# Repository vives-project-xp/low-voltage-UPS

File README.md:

# low-voltage-UPS

Project to make a low voltage UPS.
<!-- add better description -->

# Project Repository

This repository contains the source code and documentation for our project.

## Repository Structure

- `case`: Contains files related to the project's case design and 3D models.
- `esp-code`: Contains the code for the ESP micro controller used in the project.
- `frontend`: Contains the web frontend code for the project.
- `home-assistant`: Contains the configuration files for integrating the project with Home Assistant.
- `pcb`: Contains the PCB design files.
- `schemas`: Contains the schema diagrams for the project.

Link to video and ppt:
[Onedrive](https://vivesonline-my.sharepoint.com/:f:/g/personal/r0782899_student_vives_be/ErkIe6ZSpKdGq8MmYVde3NIBA33tiSL_xVnvaDJGF-avBQ?e=PaFOph)

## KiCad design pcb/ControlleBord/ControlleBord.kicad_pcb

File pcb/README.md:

# Circuit Board

## To do

1. vermogen verbruik van de aangesloten toestel.
2. gaten in de pcb maken.
3. kiezen tussen de batterij en net.
4. io pinnen maken 
5. soon^tm

## Schematic

## PCB

| Front | Back |
|---|---|
|  |  |

## BOM

The BOM or Bill of Materials consists out of a list of all the components with some of theire properties. 

| Designator | Quantity | Description | Footprint | Farnell ordercode | Price / unit |
|---|---|---|---|---|---|
| R25, R28-R30 | 4 | 1 kΩ | 0805 | [2073606](https://be.farnell.com/multicomp/mcmr08x1001ftl/res-1k-1-0-125w-0805-ceramic/dp/2073606) | 0,0165 € |
| R19 | 1 | 47.5 kΩ | 0805 | [2447665](https://be.farnell.com/multicomp/mcwr08x4752ftl/res-47k5-1-0-125w-thick-film/dp/2447665) | 0,0077 € |
| R18 | 1 | 22.1 kΩ | 0805 | [3496003](https://be.farnell.com/yageo/rc0805fr-0722k1l/res-22k1-1-0-125w-0805-thick-film/dp/3496003) | 0,029 € |
| R16, R17, R20, R22, R23 | 5 | 10 kΩ | 0805 | [1612522](https://be.farnell.com/bourns/cr0805-fx-1002elf/res-10k-1-0-125w-0805-thick-film/dp/1612522) | 0,029 € |
| R15 | 1 | 3.9 kΩ | 0805 | [2447654](https://be.farnell.com/multicomp/mcwr08x3901ftl/res-3k9-1-0-125w-thick-film/dp/2447654) | 0,0078 € |
| R14 | 1 | 1.5 kΩ | 0805 | [9333924](https://be.farnell.com/multicomp/mc01w080551k5/res-1k5-5-0-1w-0805-thick-film/dp/9333924) | 0,0153 € |
| R9 | 1 | 150 kΩ | 0805 | [2447573](https://be.farnell.com/multicomp/mcwr08x1503ftl/res-150k-1-0-125w-thick-film/dp/2447573) | 0,0078 € |
| R7, R8, R11-R13 | 5 | 10 Ω | 0805 | [2331768](https://be.farnell.com/te-connectivity/crgh0805j10r/res-10r-5-0-33w-0805-thick-film/dp/2331768) | 0,0132 € |
| R3-R5, R12, R13, R15 | 6 | 0.1 Ω | 0805 | [3994646](https://be.farnell.com/walsin/ww08xr100ftl/res-r100-0-125w-0805-thick-film/dp/3994646?st=shunt%20resistor) | 0,0302 € |
| R5 | 1 | 9.1 kΩ | 0805 | [2447739](https://be.farnell.com/multicomp/mcwr08x9101ftl/res-9k1-1-0-125w-thick-film/dp/2447739) | 0,0078 € |
| R4 | 1 | 82 kΩ | 0805 | [9237860](https://be.farnell.com/yageo/rc0805fr-0782kl/res-82k-1-0-125w-0805-thick-film/dp/9237860) | 0,029 € |
| R3 | 1 | 18 kΩ | 0805 | [2447584](https://be.farnell.com/multicomp/mcwr08x1802ftl/res-18k-1-0-125w-thick-film/dp/2447584) | 0,0078 € |
| R2 | 1 | 47 kΩ | 0805 | [9237836](https://be.farnell.com/yageo/rc0805fr-0747kl/res-47k-1-0-125w-0805-thick-film/dp/9237836) | 0,042 € |
| R1 | 1 | 51 kΩ | 0805 | [2447680](https://be.farnell.com/multicomp/mcwr08x5102ftl/res-51k-1-0-125w-0805-thick-film/dp/2447680) | 0,0081 € |
|---|---|---|---|---|---|
| C2 | 1 | 2.2 pF | 0805 | [3764575](https://be.farnell.com/yageo/cc0805crnpo9bn2r2/cap-2-2pf-50v-mlcc-0805/dp/3764575) | 0,0456 € |
| C5 | 1 | 47 pF | 0805 | [2812152](https://be.farnell.com/wurth-elektronik/885012007032/cap-47pf-25v-5-c0g-np0-0805/dp/2812152) | 0,047 € |
| C6, C7, C13, C17, C23 | 5 | 1μF | 0805 | [3873501](https://be.farnell.com/yageo/cc0805kkx6s8bb105/cap-1uf-25v-mlcc-0805/dp/3873501) | 0,0375 € |
| C8 | 1 | 10 nF | 0805 | [2534062](https://be.farnell.com/wurth-elektronik/885012207066/cap-0-01-f-25v-10-x7r-0805/dp/2534062) | 0,037 € |
| C3, C4, C10, C24 | 4 | 10 μF | 0805 | [3013452](https://be.farnell.com/samsung-electro-mechanics/cl21a106kaynnne/cap-10uf-25v-mlcc-0805/dp/3013452) | 0,073 € |
| C1, C11 | 1 | 470 μF | Radial Leaded | [9451439](https://be.farnell.com/multicomp/mcgpr50v477m13x21/cap-470-f-50v-20/dp/9451439) | 0,546 € |
| C12, C22 | 2 | 22 μF | 0805 | [1907510](https://be.farnell.com/murata/grm21br61e226me44l/cap-22-f-25v-20-x5r-0805/dp/1907510) | 0,178 € |
| C14 | 1 | 15 nF | 0805 | [2812419](https://be.farnell.com/wurth-elektronik/885012207067/cap-0-015-f-25v-10-x7r-0805/dp/2812419) | 0,0344 € |
| C9, C15, C19, C21, C23-C26, C29, C30 | 10 | 0.1 μF | 0805 | [2522443](https://be.farnell.com/kemet/c0805c104z3vactu/cap-0-1-f-25v-y5v-0805/dp/2522443) | 0,033 € |
| C16 | 1 | 2.2 μF | 0805 | [2073606](https://be.farnell.com/samsung-electro-mechanics/cl21a225kafnnne/cap-2-2uf-25v-mlcc-0805/dp/3013458) | 0,049 € |
| C18 | 1 | 33 μF | 1206 | [2525171](https://be.farnell.com/tdk/c3216x5r1e336m160ac/cap-33-f-25v-20-x5r-1206/dp/2525171) | 0,826 € |
| C20 | 1 | 100 pF | 0805 | [2812409](https://be.farnell.com/wurth-elektronik/885012207054/cap-100pf-25v-10-x7r-0805/dp/2812409) | 0,0468 € |
|---|---|---|---|---|---|
| J1, J2, J4 | 3 | 2 ways | screw terminal | [3810178](https://be.farnell.com/amphenol-anytek/yo0221500000g/tb-wire-to-brd-r-a-2way-16awg/dp/3810178) | 0,455 € |
|---|---|---|---|---|---|
| U7-U10, U13, U15 | 6 | Switch | Switch | [2320087](https://be.farnell.com/c-k-components/pts645sm43smtr92lfs/switch-spst-0-05a-12vdc-smd-4/dp/2320087) | 0,25 € |
|---|---|---|---|---|---|
| J5 | 1 | USB connector | USB | [2554980](https://be.farnell.com/hirose-hrs/zx62d-b-5p8-30/micro-usb-2-0-type-b-rcpt-smt/dp/2554980?st=zx62d-b-5p8) | 0,846 € |
| U14 | 1 | ESD Protection Device | SOT-23 | [2290332](https://be.farnell.com/kingbright/kp-2012seck/led-0805-250mcd-orange/dp/2290332) | 0,159 € |
|---|---|---|---|---|---|
| SR1 | 1 | diode | DO-214 | [2101195](https://be.farnell.com/multicomp/ss34a/diode-rectifier-3a-40v-do-214ac/dp/2101195?st=ss34) | 0,401 € |
| D1 - D3 | 3 | led | 0805 | [2101195](https://be.farnell.com/multicomp/ss34a/diode-rectifier-3a-40v-do-214ac/dp/2101195?st=ss34) | 0,401 € |
|---|---|---|---|---|---|
| U6 | 1 | I2c potentiometer | MSOP | [8737606](https://be.farnell.com/microchip/mcp4531-103e-ms/dpot-single-7bit-v-i2c-8msop/dp/1698946?st=digital%20potentiometer) |0,40 € |
|---|---|---|---|---|---|
| L1 | 1 | 6.8 μH | YUP | [3518424](https://nl.farnell.com/wurth-elektronik/7447720068/inductor-6-8uh-unshielded-3-9a/dp/3518424) | € 0,756 |
| L2 | 1 | 33 μH | YUP | [2061655](https://nl.farnell.com/bourns/srn6045-330m/inductor-33uh-semi-shielded-power/dp/2061655) | € 0,408 |
| L3 | 1 | 49 μH | YUP | [3517136](https://nl.farnell.com/wurth-elektronik/744132/toroidal-inductor-49uh-5-8a-tht/dp/3517136) | € 2,56 |
|---|---|---|---|---|---|
| U3, U5 | 1 | 10 kΩ | SOIC | [3517136](https://be.farnell.com/texas-instruments/ina219bidr/current-power-monitor-11khz-soic/dp/3118166?st=ina219) | 2,96 € |
|---|---|---|---|---|---|
| U1 | 1 | Buck | SOIC | [3755444](https://be.farnell.com/diodes-inc/pam2421aecadjr/dc-dc-conv-boost-520khz-40-to/dp/3755444?st=pam2421) | 0,90 € |
| U2 | 1 | Buck| SOIC | [4064213](https://be.farnell.com/stmicroelectronics/l6981c33dr/dc-dc-conv-sync-buck-400khz-150deg/dp/4064213?st=l6981c) | 3,02 € |
| U4 | 1 | Buck | QFN-34 | [2355372](https://be.farnell.com/onsemi/fan23sv10mmpx/buck-synch-adj-10a-1-5mhz-34pqfn/dp/2355372?st=fan23sv10m) | 1,72 € |
|---|---|---|---|---|---|
| Q2 | 1 | P-kanaal | TO-220 | [8648620](https://be.farnell.com/infineon/irf9540npbf/mosfet-p-100v-23a-to-220/dp/8648620) | 1,55 € |
| Q1 | 1 | N-kanaal | TO-220 | [2547307](https://be.farnell.com/vishay/irfz34pbf/mosfet-n-ch-60v-30a-to-220ab-3/dp/2547307) | 1,96 € |

Total price: 65,03 €

| Designator | Quantity | Description | Footprint | Mouser ordercode | Price / unit |
|---|---|---|---|---|---|
| U12 | 1 | ESP32-S3 | ESP32 | [C2913202](https://www.lcsc.com/product-detail/WiFi-Modules_Espressif-Systems-ESP32-S3-WROOM-1-N16R8_C2913202.html) | € 4.83 |
| U11 | 1 | CP2102NA02GQFN28 | QFN28 | [C964632](https://www.lcsc.com/product-detail/USB-ICs_SILICON-LABS-CP2102N-A02-GQFN28R_C964632.html) | € 2.60 |

Total price: €10.26

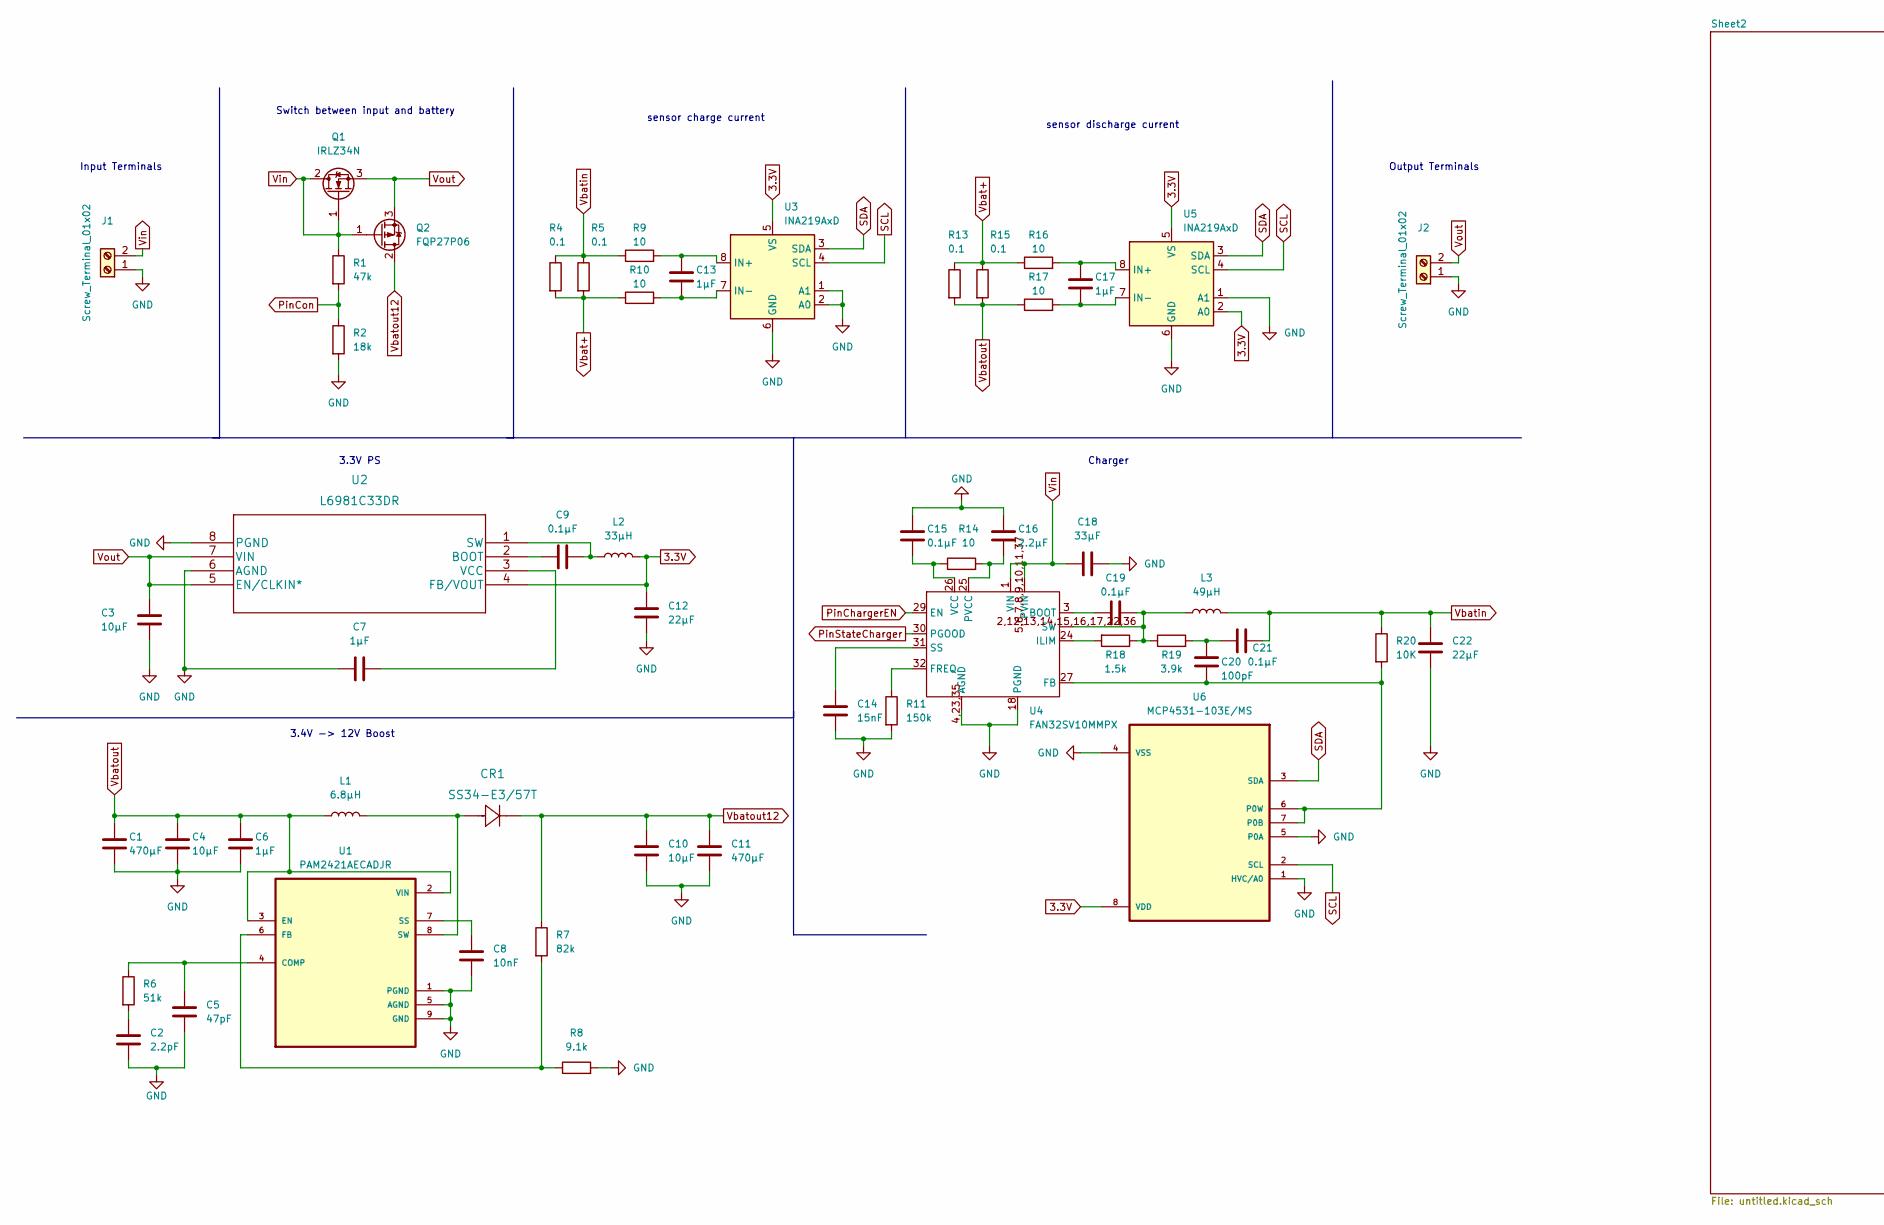
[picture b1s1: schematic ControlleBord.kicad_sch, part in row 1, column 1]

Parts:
C1, C11: 470μF; CP_Radial_D13.0mm_P5.00mm
C2: 2.2pF; C_0805_2012Metric
C3, C4, C10: 10μF; C_0805_2012Metric
C5: 47pF; C_0805_2012Metric
C6, C7, C13, C17: 1μF; C_0805_2012Metric
C8: 10nF; C_0805_2012Metric
C9, C15, C19, C21: 0.1μF; C_0805_2012Metric
C12, C22: 22μF; C_0805_2012Metric
C14: 15nF; C_0805_2012Metric
C16: 2.2μF; C_0805_2012Metric
C18: 33μF; C_1206_3216Metric
C20: 100pF; C_0805_2012Metric
CR1: SS34-E3/57T; SS34-E3&slash_57T
J1, J2: Screw_Terminal_01x02; YO0221500000G
L1: 6.8μH; L_Toroid_Vertical_L26.7mm_W14.0mm_P10.16mm_Pulse_D
L2: 33μH; L_Bourns_SRN6045TA
L3: 49μH; L_Toroid_Vertical_L21.6mm_W9.1mm_P8.40mm_Bourns_5700
Q1: IRLZ34N; TO-220-3_Vertical
Q2: FQP27P06; TO-220-3_Vertical
R1: 47k; R_0805_2012Metric
R2: 18k; R_0805_2012Metric
R4, R5, R13, R15: 0.1; R_2512_6332Metric
R6: 51k; R_0805_2012Metric
R7: 82k; R_0805_2012Metric
R8: 9.1k; R_0805_2012Metric
R9, R10, R14, R16, R17: 10; R_0805_2012Metric
R11: 150k; R_0805_2012Metric
R18: 1.5k; R_0805_2012Metric
R19: 3.9k; R_0805_2012Metric
R20: 10K; R_0805_2012Metric
U1: PAM2421AECADJR; SOIC127P600X175-8N
U2: L6981C33DR
U3, U5: INA219AxD; SOIC-8_3.9x4.9mm_P1.27mm
U4: FAN32SV10MMPX; FAN23SV10M
U6: MCP4531-103E/MS; SOP65P490X110-8N

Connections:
3.3V: C12.1, L2.2, U2.4 (FB/VOUT), U3.5 (VS), U5.2 (A0), U5.5 (VS), U6.8 (VDD); also elsewhere on the board
GND: C1.2, C2.2, C3.2, C4.2, C5.2, C6.2, C7.1, C8.2, C10.2, C11.2, C12.2, C14.2, C15.1, C16.1, C18.2, C22.2, J1.1, J2.1, R2.2, R8.2, R11.2, U1.1 (PGND), U1.5 (AGND), U1.9 (GND), U2.6 (AGND), U2.8 (PGND), U3.1 (A1), U3.2 (A0), U3.6 (GND), U4.4,23,35 (AGND), U4.18 (PGND), U5.1 (A1), U5.6 (GND), U6.1 (HVC/A0), U6.4 (VSS), U6.5 (P0A); also elsewhere on the board
unnamed: C2.1, R6.2
unnamed: C5.1, R6.1, U1.4 (COMP)
unnamed: C7.2, U2.3 (VCC)
unnamed: C8.1, U1.7 (SS)
unnamed: C9.1, U2.2 (BOOT)
unnamed: C9.2, L2.1, U2.1 (SW)
unnamed: C13.1, R9.2, U3.8 (IN+)
unnamed: C13.2, R10.2, U3.7 (IN-)
unnamed: C14.1, U4.31 (SS)
unnamed: C15.2, R14.1, U4.26 (VCC)
unnamed: C16.2, R14.2, U4.25 (PVCC)
unnamed: C17.1, R16.2, U5.8 (IN+)
unnamed: C17.2, R17.2, U5.7 (IN-)
unnamed: C19.1, U4.3 (BOOT)
unnamed: C19.2, L3.1, R18.1, R19.1, U4.2,12,13,14,15,16,17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 (SW)
unnamed: C20.1, C21.1, R19.2
unnamed: C20.2, R20.2, U4.27 (FB), U6.6 (P0W), U6.7 (P0B)
unnamed: CR1.2, L1.2, U1.8 (SW)
unnamed: R7.2, R8.1, U1.6 (FB)
unnamed: R11.1, U4.32 (FREQ)
unnamed: R18.2, U4.24 (ILIM)
PinChargerEN: U4.29 (EN); also elsewhere on the board
PinCon: R1.2, R2.1; also elsewhere on the board
PinStateCharger: U4.30 (PGOOD); also elsewhere on the board
SCL: U3.4 (SCL), U5.4 (SCL), U6.2 (SCL); also elsewhere on the board
SDA: U3.3 (SDA), U5.3 (SDA), U6.3 (SDA); also elsewhere on the board
Vbat+: R4.2, R5.2, R10.1, R13.1, R15.1, R16.1; also elsewhere on the board
Vbatin: C21.2, C22.1, L3.2, R4.1, R5.1, R9.1, R20.1
Vbatout: C1.1, C4.1, C6.1, L1.1, R13.2, R15.2, R17.1, U1.2 (VIN), U1.3 (EN); also elsewhere on the board
Vbatout12: C10.1, C11.1, CR1.1, Q2.2 (D), R7.1; also elsewhere on the board
Vin: C18.1, J1.2, Q1.1 (G), Q1.2 (D), Q2.1 (G), R1.1, U4.1 (VIN), U4.5,6,7,8,9,10,11,37 (PVIN)
Vout: C3.1, J2.2, Q1.3 (S), Q2.3 (S), U2.5 (EN/CLKIN*), U2.7 (VIN)

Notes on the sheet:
Charger
Input Terminals
Switch between input and battery
sensor charge current
sensor discharge current
Output Terminals
3.3V PS
3.4V -> 12V Boost

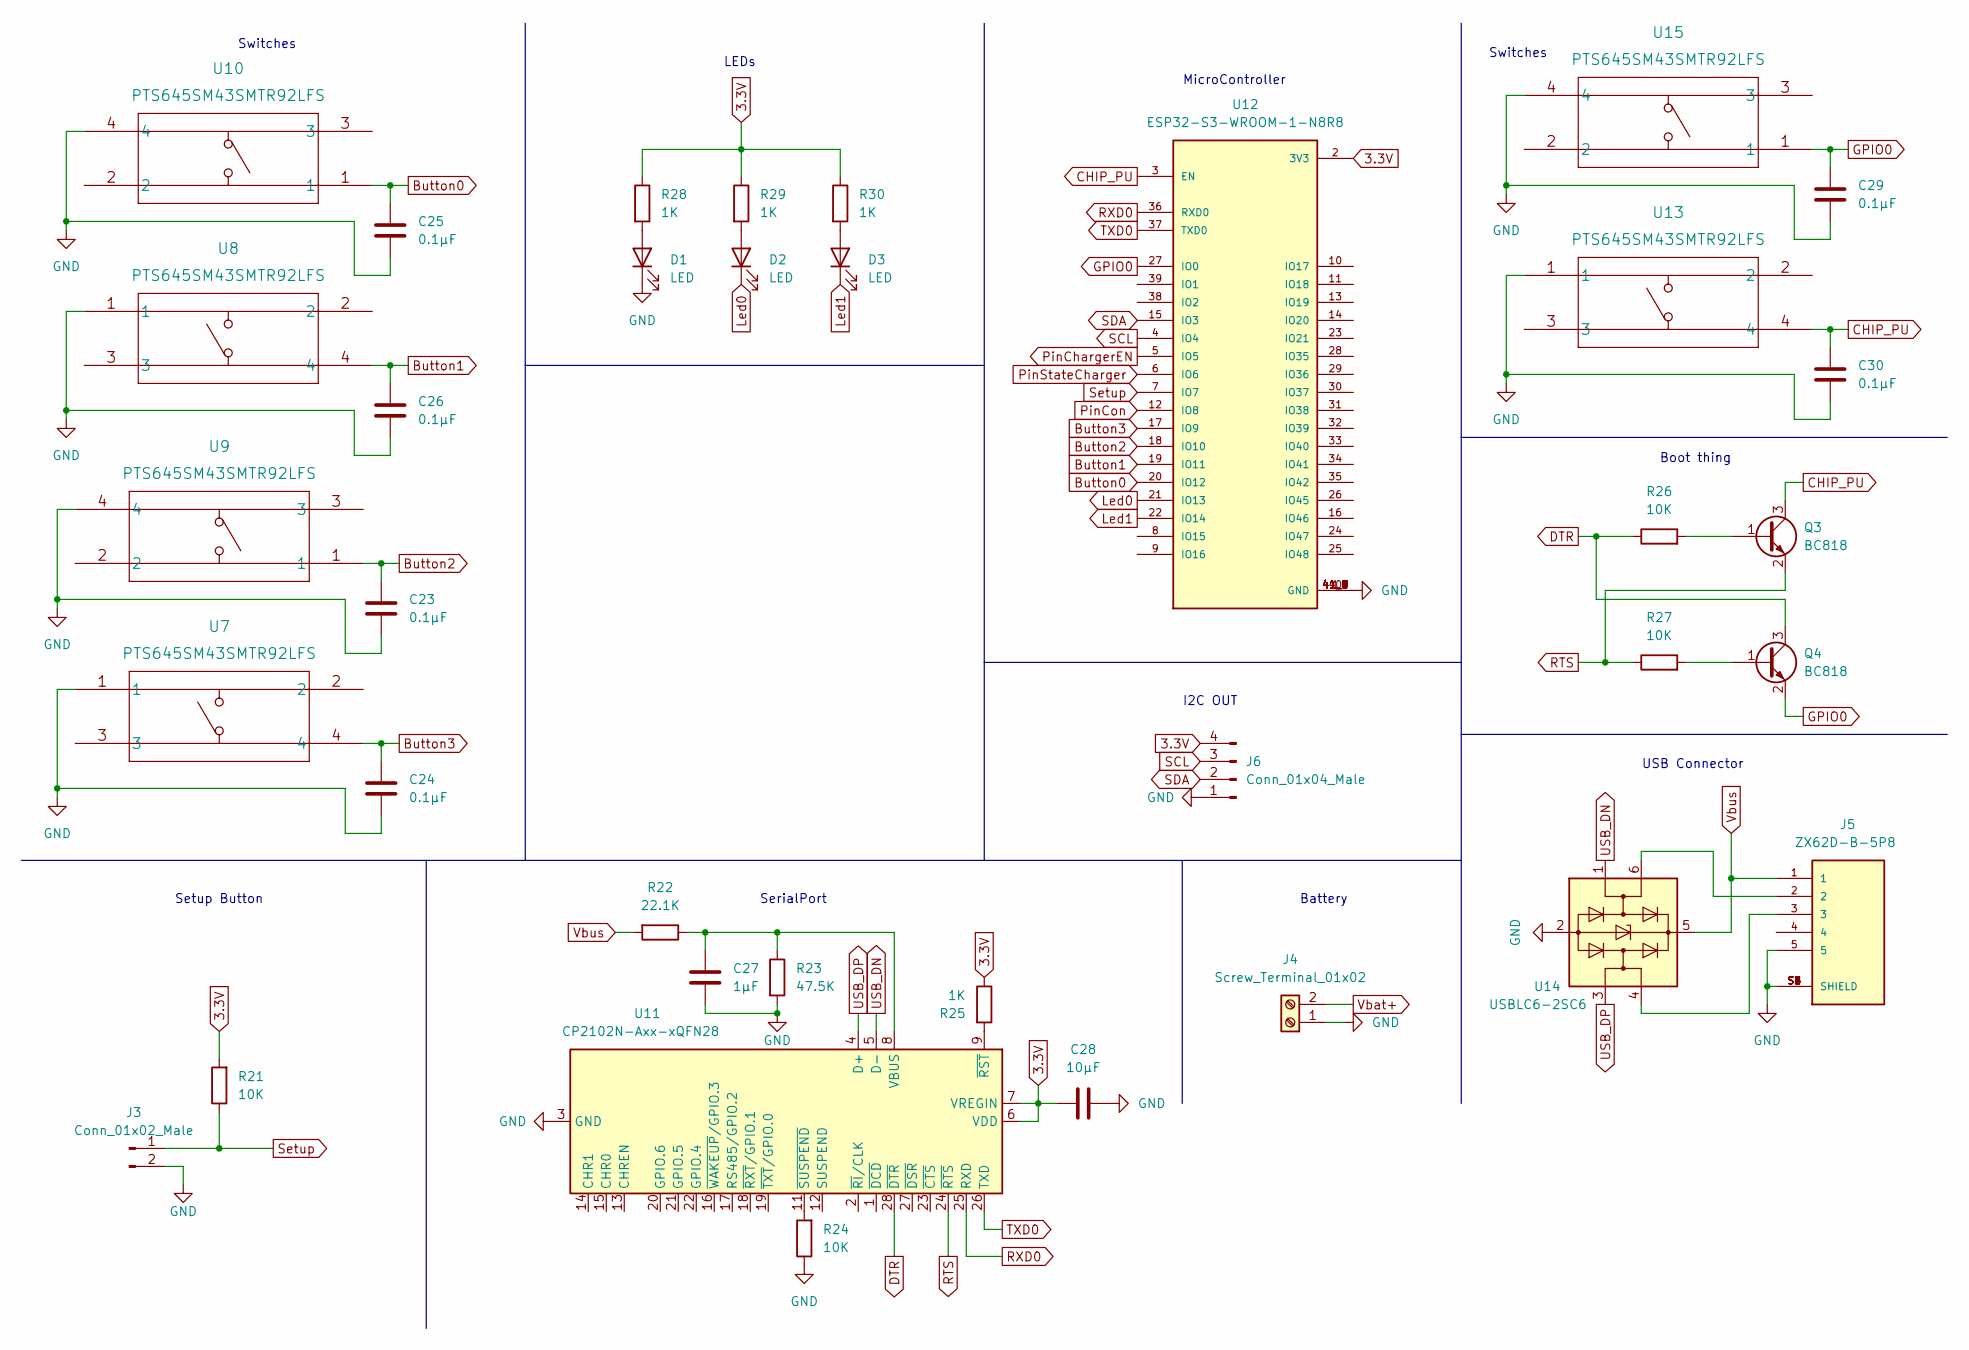
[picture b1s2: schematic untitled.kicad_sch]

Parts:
C23, C24, C25, C26, C29, C30: 0.1μF; C_0805_2012Metric
C27: 1μF; C_0805_2012Metric
C28: 10μF; C_0805_2012Metric
D1, D2, D3: LED; R_0805_2012Metric
J3: Conn_01x02_Male; PinHeader_1x02_P2.54mm_Vertical
J4: Screw_Terminal_01x02; YO0221500000G
J5: ZX62D-B-5P8; HRS_ZX62D-B-5P8; PARTREV N/A
J6: Conn_01x04_Male; PinSocket_1x04_P2.54mm_Vertical
Q3, Q4: BC818; SOT-23
R21, R24, R26, R27: 10K; R_0805_2012Metric
R22: 22.1K; R_0805_2012Metric
R23: 47.5K; R_0805_2012Metric
R25, R28, R29, R30: 1K; R_0805_2012Metric
U7, U8, U9, U10, U13, U15: PTS645SM43SMTR92LFS
U11: CP2102N-Axx-xQFN28; QFN-28-1EP_5x5mm_P0.5mm_EP3.35x3.35mm
U12: ESP32-S3-WROOM-1-N8R8; XCVR_ESP32S3WROOM1N8R8
U14: USBLC6-2SC6; SOT-23-6

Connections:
3.3V: C28.1, J6.4, R21.2, R25.1, R28.1, R29.1, R30.1, U11.6 (VDD), U11.7 (VREGIN), U12.2 (3V3); also elsewhere on the board
Button0: C25.2, U10.1, U12.20 (IO12)
Button1: C26.1, U8.4, U12.19 (IO11)
Button2: C23.2, U9.1, U12.18 (IO10)
Button3: C24.1, U7.4, U12.17 (IO9)
CHIP_PU: C30.1, Q3.3 (C), U12.3 (EN), U13.4
DTR: Q4.3 (C), R26.1, U11.28 (~DTR)
GND: C23.1, C24.2, C25.1, C26.2, C27.2, C28.2, C29.1, C30.2, D1.1 (K), J3.2, J4.1, J5.5, J5.S1 (SHIELD), J5.S2 (SHIELD), J5.S3 (SHIELD), J5.S4 (SHIELD), J5.S5 (SHIELD), J5.S6 (SHIELD), J6.1, R23.2, R24.1, U7.1, U8.1, U9.4, U10.4, U11.3 (GND), U11.29 (GND), U12.1 (GND), U12.40 (GND), U12.41_1 (GND), U12.41_2 (GND), U12.41_3 (GND), U12.41_4 (GND), U12.41_5 (GND), U12.41_6 (GND), U12.41_7 (GND), U12.41_8 (GND), U12.41_9 (GND), U13.1, U14.2 (GND), U15.4; also elsewhere on the board
GPIO0: C29.2, Q4.2 (E), U12.27 (IO0), U15.1
Led0: D2.1 (K), U12.21 (IO13)
Led1: D3.1 (K), U12.22 (IO14)
unnamed: C27.1, R22.1, R23.1, U11.8 (VBUS)
unnamed: D1.2 (A), R28.2
unnamed: D2.2 (A), R29.2
unnamed: D3.2 (A), R30.2
unnamed: J5.2, U14.6 (I/O1)
unnamed: J5.3, U14.4 (I/O2)
unnamed: Q3.1 (B), R26.2
unnamed: Q4.1 (B), R27.2
unnamed: R24.2, U11.11 (~SUSPEND)
unnamed: R25.2, U11.9 (~RST)
PinChargerEN: U12.5 (IO5); also elsewhere on the board
PinCon: U12.12 (IO8); also elsewhere on the board
PinStateCharger: U12.6 (IO6); also elsewhere on the board
RTS: Q3.2 (E), R27.1, U11.24 (~RTS)
RXD0: U11.25 (RXD), U12.36 (RXD0)
SCL: J6.3, U12.4 (IO4); also elsewhere on the board
SDA: J6.2, U12.15 (IO3); also elsewhere on the board
Setup: J3.1, R21.1, U12.7 (IO7)
TXD0: U11.26 (TXD), U12.37 (TXD0)
USB_DN: U11.5 (D-), U14.1 (I/O1)
USB_DP: U11.4 (D+), U14.3 (I/O2)
Vbat+: J4.2; also elsewhere on the board
Vbus: J5.1, R22.2, U14.5 (VBUS)

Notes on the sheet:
SerialPort
USB Connector
Setup Button
Switches
MicroController
LEDs
Battery
I2C OUT
Boot thing

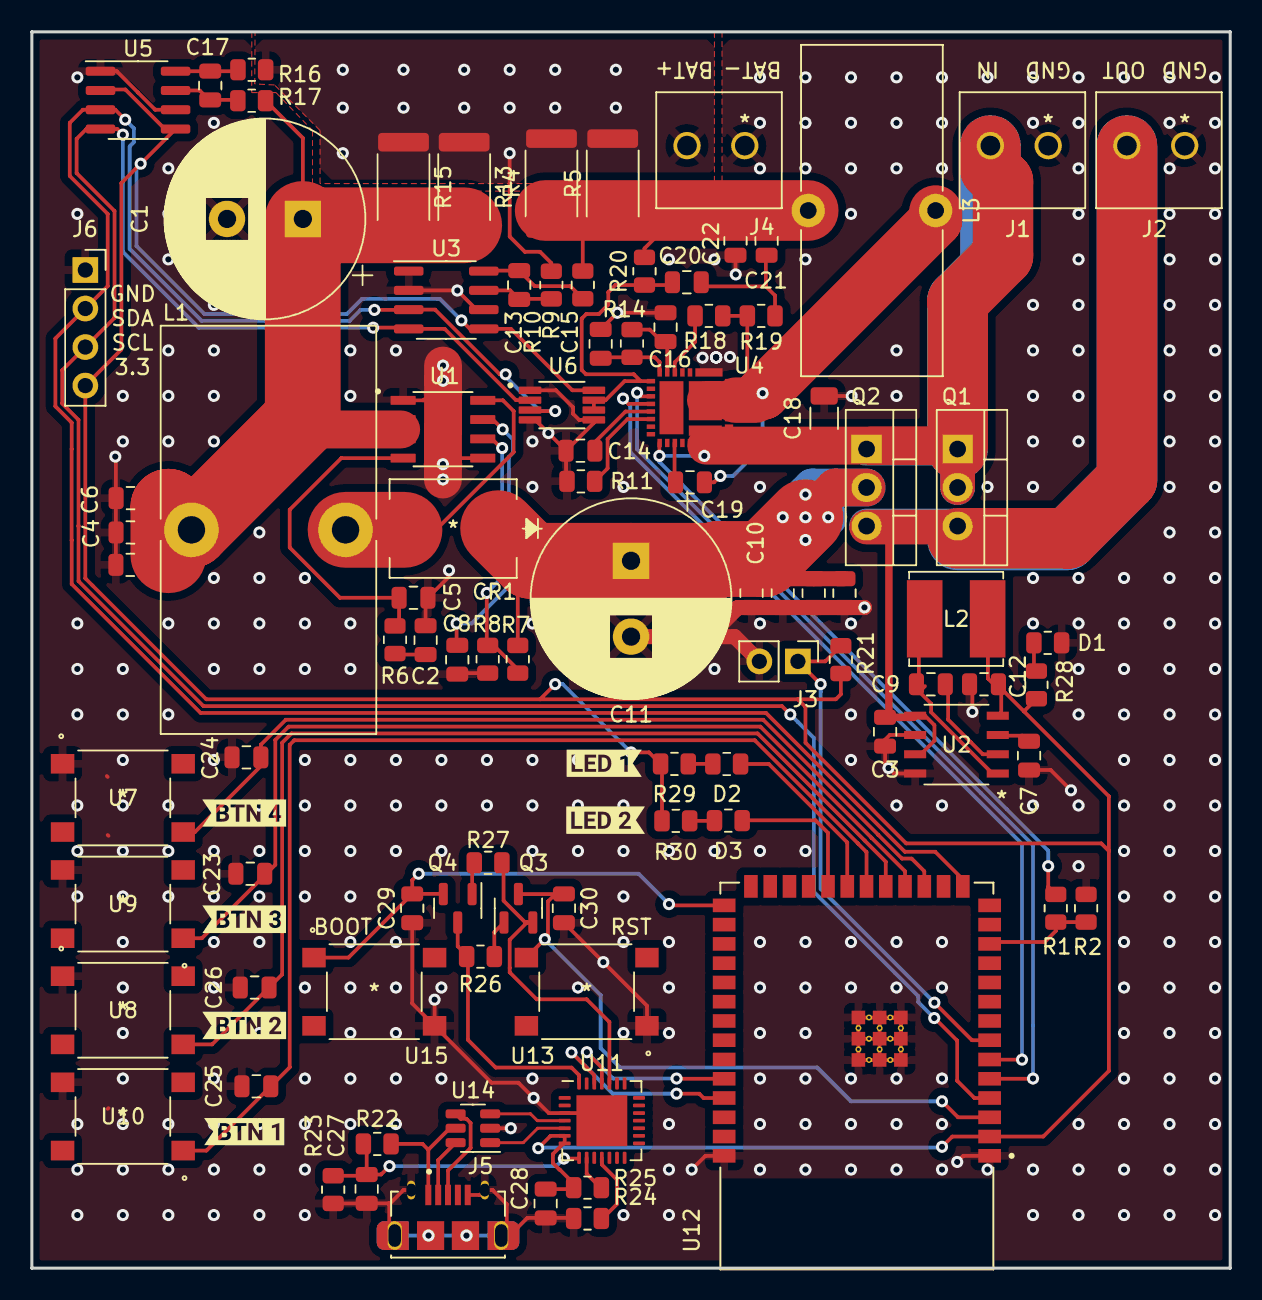
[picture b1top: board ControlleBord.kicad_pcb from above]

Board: 2 copper layers, 79.0 x 81.5 mm, 100 parts (0 on the bottom side), 60 nets.

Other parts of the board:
C4#2, C10#2, C10#3, C10#4: 10μF; C_0805_2012Metric
kibuzzard-6409D4B5: G***; kibuzzard-6409D4B5
kibuzzard-6409D4BC: G***; kibuzzard-6409D4BC
kibuzzard-6409D4C2: G***; kibuzzard-6409D4C2
kibuzzard-6409D4D1: G***; kibuzzard-6409D4D1
kibuzzard-6409D47A: G***; kibuzzard-6409D47A
kibuzzard-6409D460: G***; kibuzzard-6409D460

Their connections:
GND: C4#2.2, C10#2.2, C10#3.2, C10#4.2; also elsewhere on the board
Vbatout: C4#2.1; also elsewhere on the board
Vbatout12: C10#2.1, C10#3.1, C10#4.1; also elsewhere on the board

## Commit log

2023-03-02 initial compose
2023-03-02 working docker-compose not configured yet
2023-03-02 docker compose v2
2023-03-02 Made Bom and schematics.
2023-03-02 docker compose v3
2023-03-02 Moved pcb files to folder
2023-03-03 Initial commit of frontend using nuxt (vue)
2023-03-03 added link back to homepage
2023-03-03 added very basic footer
2023-03-03 published build and added to link to readme
2023-03-03 added contact page
2023-03-03 edit content of template pages
2023-03-04 removed unnecessary div
2023-03-04 added tailwind css to project
2023-03-04 did some styling for the default layout
2023-03-05 added padding to content
2023-03-05 added drak mode (system default)
2023-03-05 fixed page mistake
2023-03-05 update Home Assistent
2023-03-05 changed theme color
2023-03-05 made homepage modular
2023-03-05 eddited layout theme
2023-03-05 added axample content to setup page
2023-03-06 adding dark-mode button
2023-03-07 just dark theme
2023-03-07 removed unnecessary file
2023-03-07 switched setup and about page on header
2023-03-08 add other plugins @nuxtjs/tailwindcss , color-mode
2023-03-08 custom style works with tailwind
2023-03-08 dropdown dark mode button
2023-03-08 custom style adds darkmode theme
2023-03-09 switched to purple theme
2023-03-09 added daisyui (tailwind plugin)
2023-03-09 removed all theming
2023-03-09 ESP code added, wifi and mqtt basic example working
2023-03-09 Switched to only one layout (inside app.vue)
2023-03-09 switched drawer to end (right side)
2023-03-09 homeassistant new working config
2023-03-09 mossquito conf update
2023-03-09 update docker compose file
2023-03-09 add groups.yaml
2023-03-09 add pcb files
2023-03-09 added imges to README.md
2023-03-09 changed header title
2023-03-09 overide custom themes
2023-03-09 added title block to home page
2023-03-09 Added fixed height to homepage title bock
2023-03-09 global update to create parallel with main branch
2023-03-13 Added more content for testing purposes
2023-03-13 fixed section spacing
2023-03-13 Created seperate Header and Footer modules
2023-03-13 Fixed header color
2023-03-13 removed hero to fix header bug, bg opacity is gone
2023-03-13 Moved back to layout file
2023-03-14 local storage mqtt data
2023-03-14 adding gitignore
2023-03-14 adding comments mosquitto.conf
2023-03-14 adding more to ha configuration
2023-03-14 update gitignore
2023-03-15 added some links to readme
2023-03-15 Added testing content to setup page
2023-03-15 added vueuse for bluetooth functionality
2023-03-15 First implementation of bluetooth
2023-03-15 added dark filter over bg image
2023-03-16 adding comments
2023-03-16 added bluetooth services and chars for testing
2023-03-16 fixing typo's
2023-03-16 fixing more typo's
2023-03-16 adding sensor
2023-03-16 Added schema's
2023-03-16 made bluetooth work (without module)
2023-03-16 fixing typo
2023-03-16 moved to export default
2023-03-16 made changess to readme
2023-03-16 misc
2023-03-16 added multiple characteristic
2023-03-18 first try at blueprint
2023-03-18 adding first try blueprint
2023-03-18 refining mqtt devices
2023-03-18 changing order
2023-03-18 trying to create automation blueprint
2023-03-18 first draft of the readme
2023-03-23 adding full config of HA localy
2023-03-23 adding local config
2023-03-23 updating gitignore
2023-03-23 show all bluetooth devices
2023-03-23 Added pagetitle component
2023-03-23 updated setup page
2023-03-23 updated ssid characteristic
2023-03-23 blueprints with deprecated group.set
2023-03-23 updating HA
2023-03-23 adding group.yaml
2023-03-23 adding dwain
2023-03-23 fixing battery charge
2023-03-23 dwains dashboard
2023-03-23 updated setup to use Composition API
2023-03-23 added page title for contact page
2023-03-23 added content to about page
2023-03-30 dwains dashboard config
2023-03-30 mqtt.yaml
2023-03-30 typo fix
2023-03-30 adding hacs
2023-03-30 adding dependencies
2023-03-30 gitignore update
2023-04-12 added first version of cdem device
2023-04-13 v2 of cdem ha integration
2023-04-13 v3 of cdem ha integration
2023-04-13 v4 of cdem ha integration
2023-04-18 Added IO map and I2C adresses to Schemas
2023-04-20 typo fix 'web site' to 'website'
2023-04-20 updating deprecated dependencties
2023-04-20 adding more function to the connect button
2023-04-20 mqtt broker input field adding default port 1883
2023-04-20 reformatted setup page
2023-04-20 added comments
2023-04-20 reformat setup page code
2023-04-20 added empty files for homeasssistant schemas
2023-04-20 adding custom css root colors
2023-04-20 adding packages color-mode, nuxtjs/tailwindcss
2023-04-20 update default text color
2023-04-20 changed file type for better loading times
2023-04-20 adding custom css class
2023-04-20 applying new css style to all pages
2023-04-20 added other drawio backup format to gitignore
2023-04-20 added some flowcharts
2023-04-20 added python cache to gitignore
2023-04-20 adding style
2023-04-20 small reformating setting page
2023-04-26 removed link to contact page
2023-04-26 changed style
2023-04-26 changed the default vue page width
2023-04-26 changed style and content of the about page
2023-04-26 changed style and content setup page
2023-04-26 added content to index page
2023-04-27 updated the todo list
2023-04-27 updated the todo list 2.0
2023-04-27 fixed mqtt port
2023-04-27 fixed ip port bug setup page
2023-04-27 added some documentation to program MCP4531
2023-04-27 added dns resolving and ip validation
2023-04-27 adjusted style and adding responsive cards
2023-04-27 made more responsive
2023-04-27 adding password viewer setup page
2023-04-27 removed redundend packages
2023-04-27 adding responsiveness
2023-04-27 adding home route to header
2023-04-27 changed style adding margin
2023-04-27 add costum device name
2023-04-27 adding name function logic
2023-04-27 adding responsivess
2023-04-27 adding name character
2023-05-01 Updated files to version 5
2023-05-01 Initial commit of lvups integration
2023-05-04 adding content
2023-05-04 adding headshots
2023-05-04 updating favicon
2023-05-04 adding responsivness
2023-05-04 deleting contact page
2023-05-04 reformat responsivness
2023-05-04 edit disconnect function
2023-05-04 error detection broker ip
2023-05-08 Release v1 of cdem integration
2023-05-08 Release v1 of lvups integration
2023-05-08 cleaned up home-assistant folder
2023-05-08 added device info to dev readme
2023-05-09 Worked on case
2023-05-09 Finished v1 of case
2023-05-09 added stl version of case parts
2023-05-09 converted case to obj for use in blender
2023-05-09 add script to import multi obj files into blender
2023-05-09 created blender project
2023-05-09 renderd still img
2023-05-09 rendered animation
2023-05-09 made gif and mp4 from animation stills
2023-05-09 Added very simple readme
2023-05-09 remove all file from hass folder (before merge)
2023-05-09 adding gif to main frontend page
2023-05-10 replacing gif with image gif in wrong format
2023-05-10 added some automation examples to the readme
2023-05-10 made some screenshots of the hass integration
2023-05-10 Added images to readme
2023-05-10 updated some of the schemas
2023-05-10 Fixed wronf mqtt adress in showcase
2023-05-10 rendered transparent image of case
2023-05-10 resized and changed file type case picture
2023-05-10 replaced picture case with transparent version
2023-05-10 update global readme
2023-05-10 Firmware flowchart bijwerken
2023-05-10 remove folder in folder
2023-05-11 added link to video and ppt
2023-05-18 moved cdem integration to other repo
2023-05-18 fixed some mistakes
2023-05-18 removed file that was used for cdem

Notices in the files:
parts and their libraries:
Copyright 2021 Accelerated Designs. All rights reserved.
